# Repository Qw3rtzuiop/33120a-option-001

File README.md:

# 33120a-option-001
External reference frequency option for the HP/Agilent/Keysight 33120a arbitrary function generator

<span style="color:red">The calibration can fail with "value range" error. I solved it by repeating the calibration 86 multiple times changing the readout frequency in small and bigger steps.</span>

The ocxo is a used Vectron C4550A1-0213 (10 MHz, 5V).

Kicad 3d render pic of the rev. 1 PCB.

The PCB is mounted on the side. You need to drill holes into the metal to mount the PCB. The pics show the rev. 0 with two bodge wires. 

Suitable isolated BNC jacks are Amphenol 112252.

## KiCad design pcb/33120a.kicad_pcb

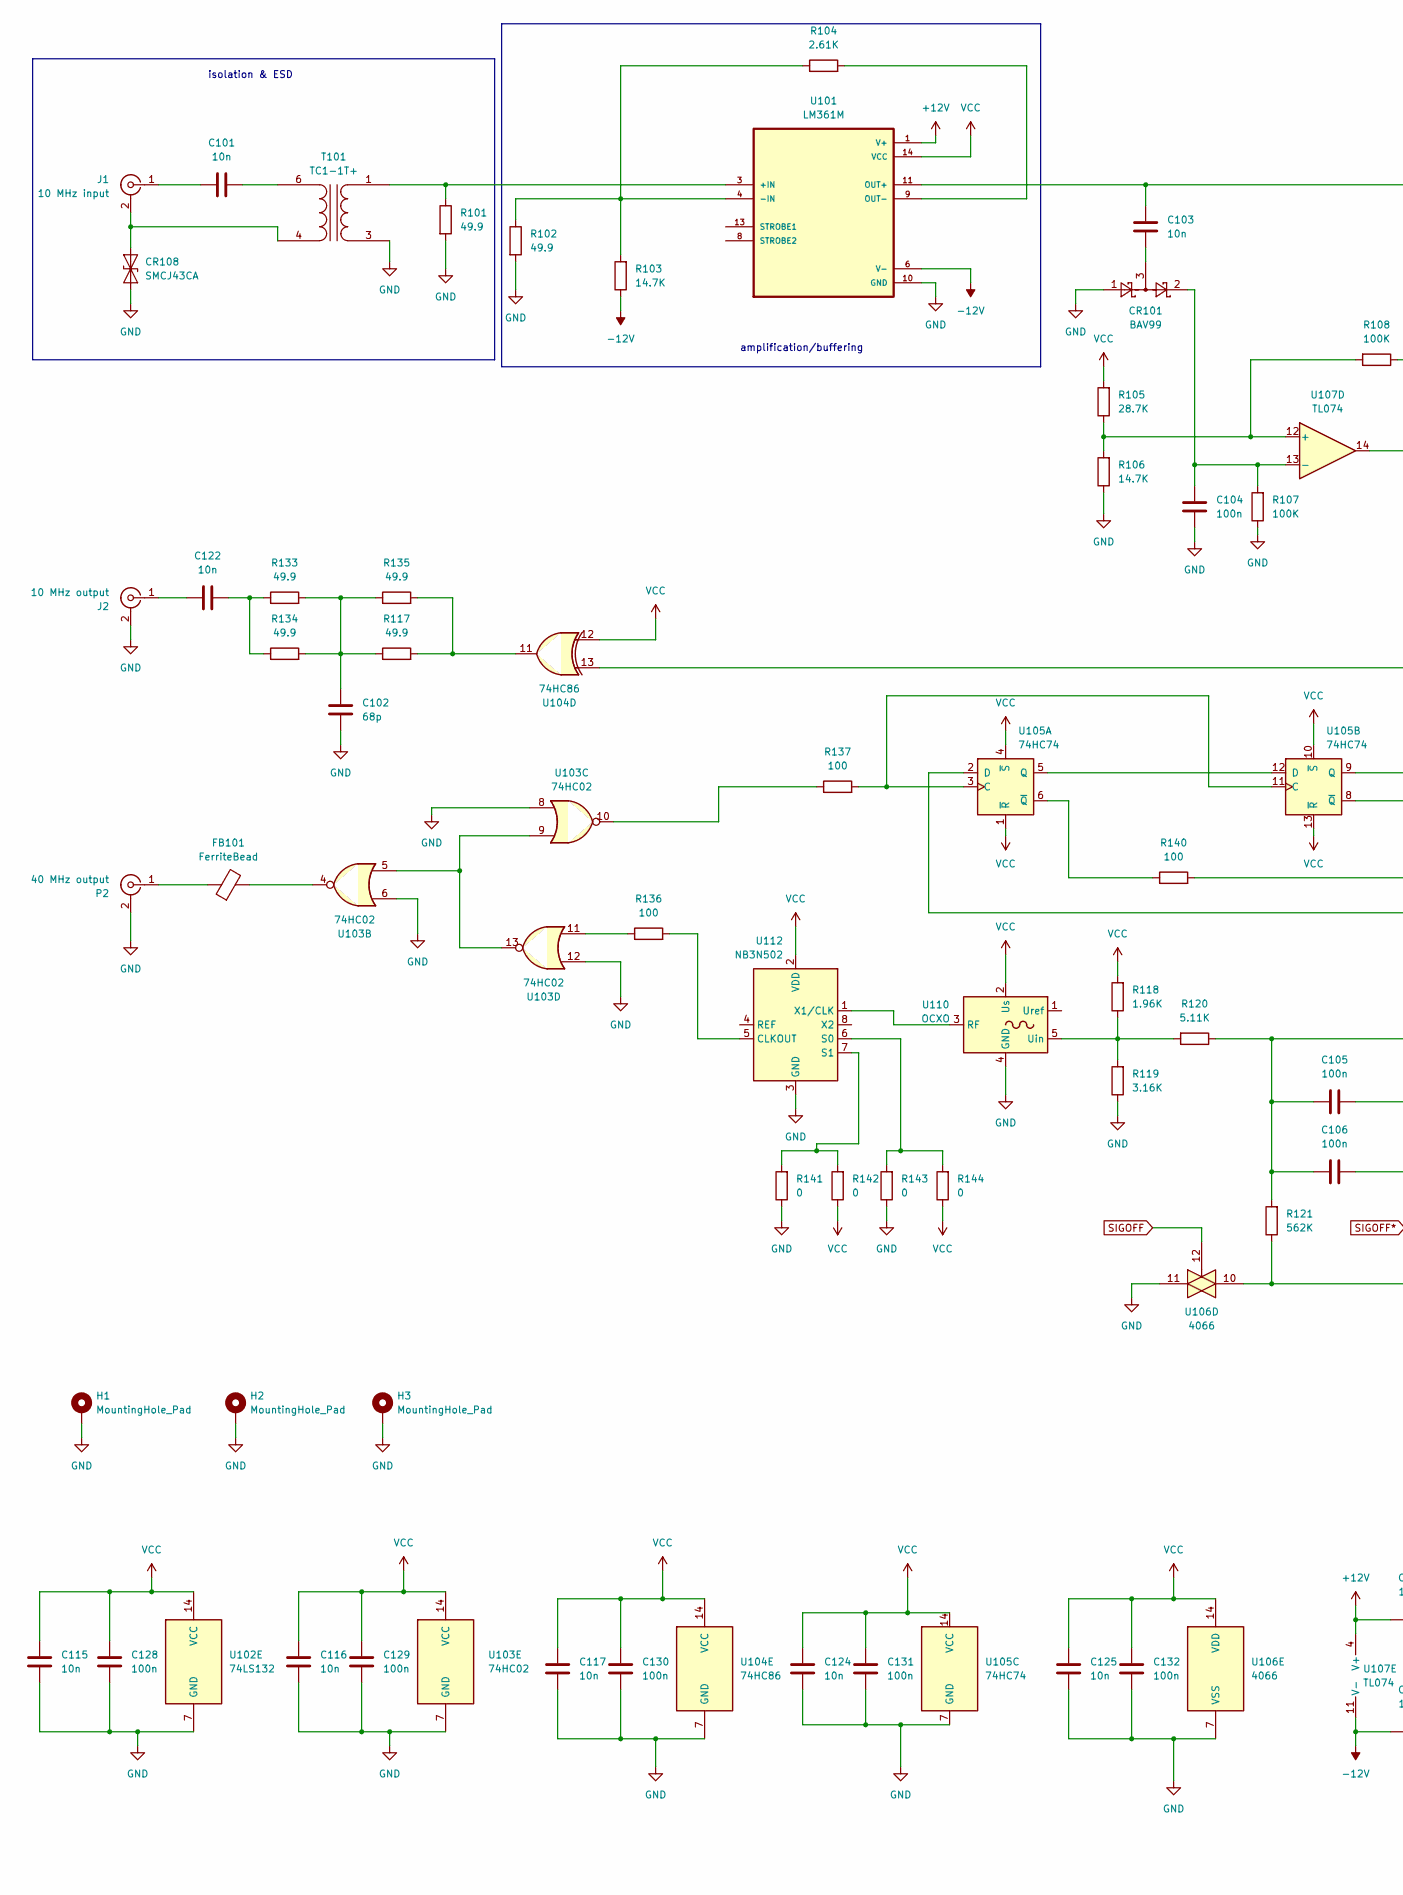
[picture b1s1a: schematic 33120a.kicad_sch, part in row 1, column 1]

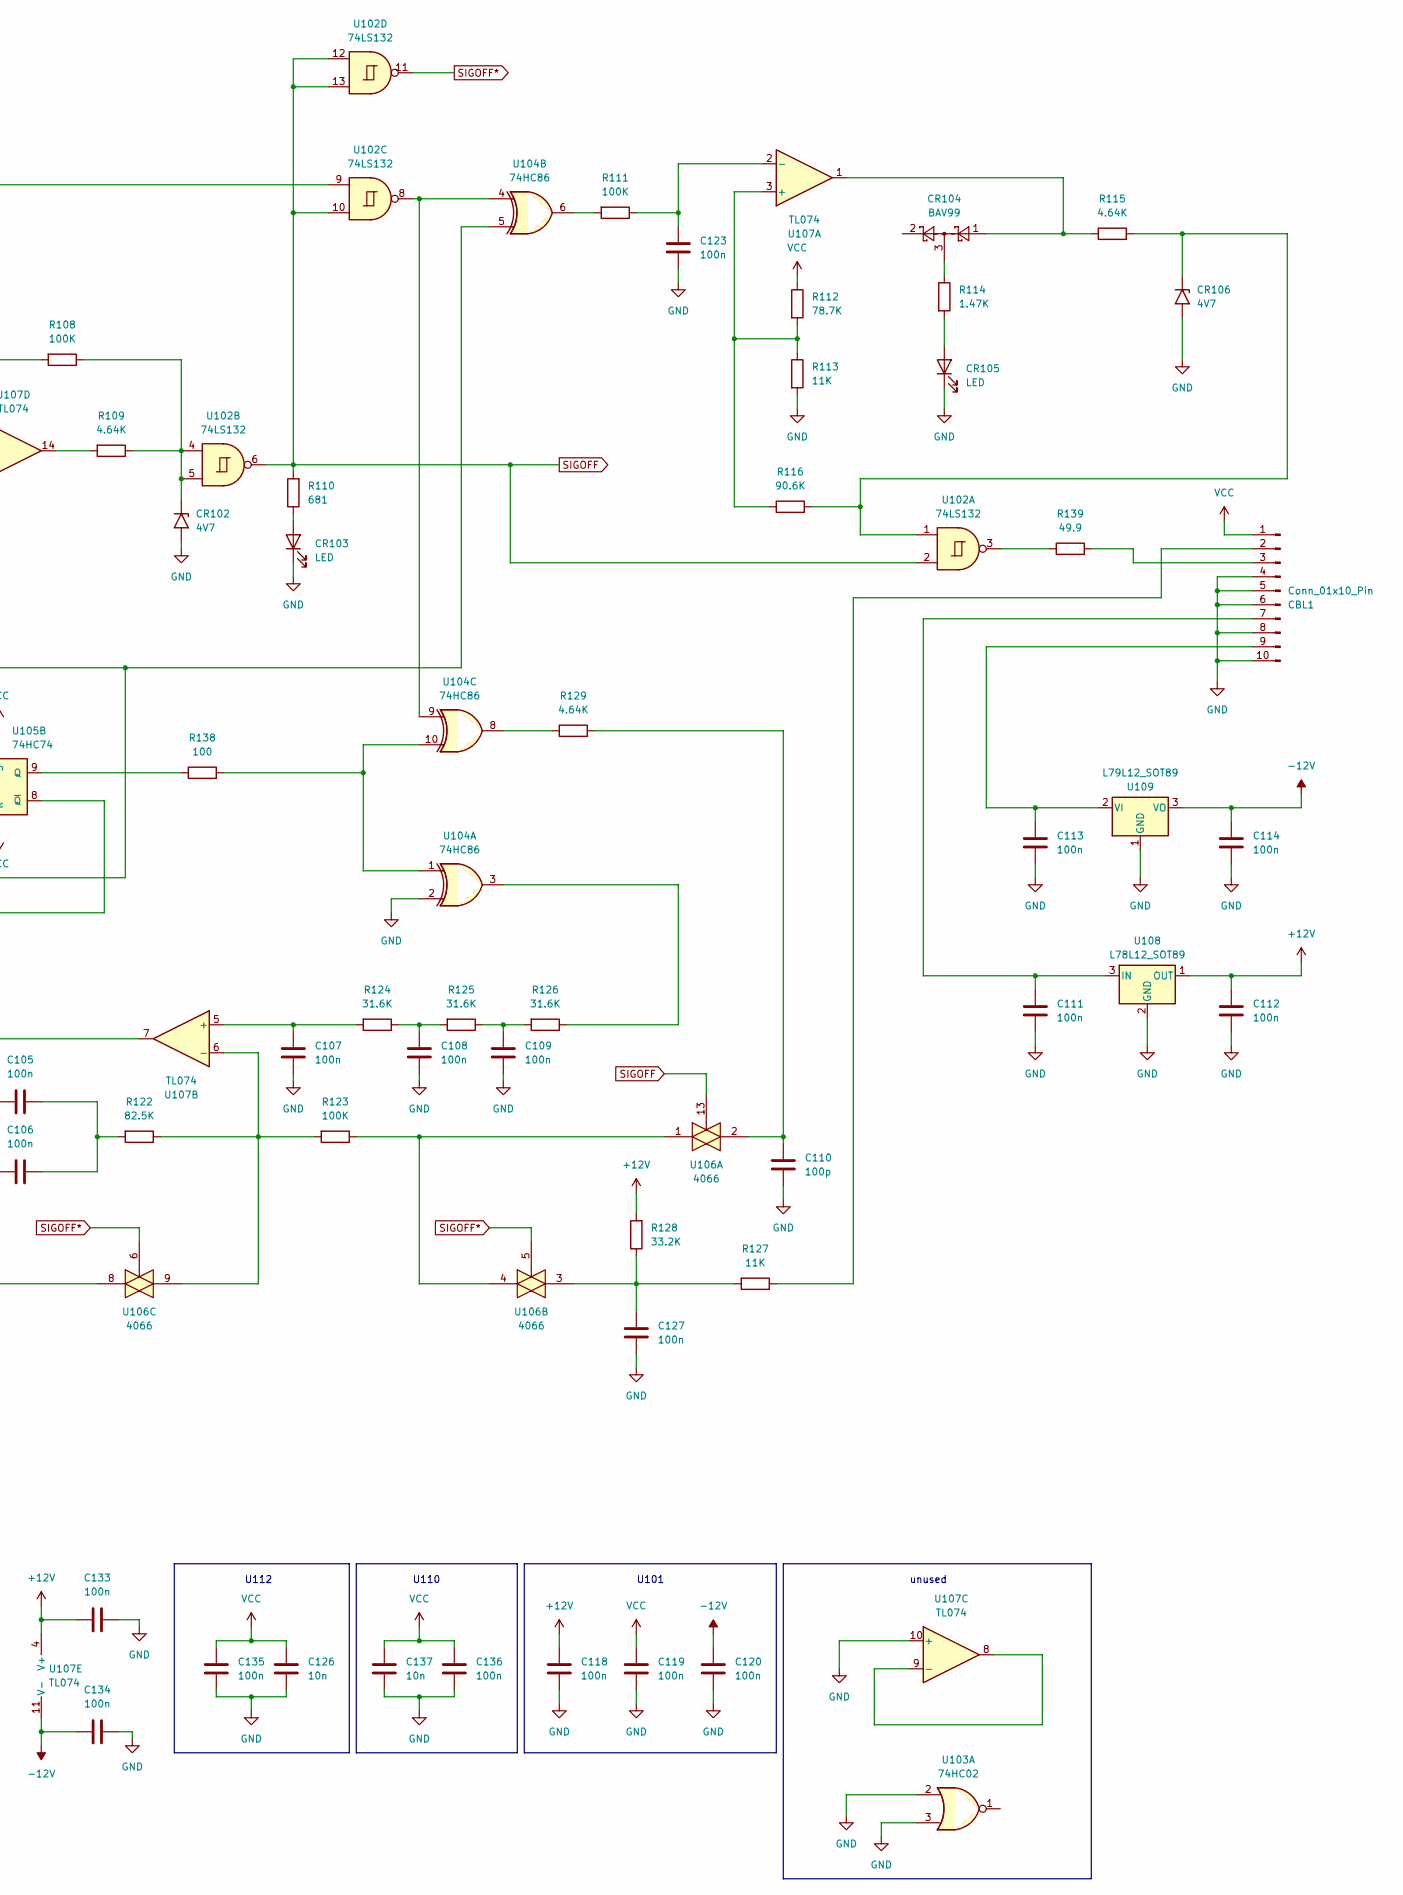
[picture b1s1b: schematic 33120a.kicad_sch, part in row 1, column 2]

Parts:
C101, C103, C115, C116, C117, C122, C124, C125, C126, C137: 10n; C_0805_2012Metric
C102: 68p; C_0805_2012Metric
C104, C105, C106, C107, C108, C109, C111, C112, C113, C114, C118, C119, C120, C123, C127, C128, C129, C130, C131, C132, C133, C134, C135, C136: 100n; C_0805_2012Metric
C110: 100p; C_0805_2012Metric
CBL1: Conn_01x10_Pin; IDC-Header_2x05_P2.54mm_Vertical
CR101, CR104: BAV99; SOT-23
CR102, CR106: 4V7; D_MiniMELF
CR103, CR105: LED; LED_0805_2012Metric
CR108: SMCJ43CA; D_SOD-128
FB101: FerriteBead; L_0805_2012Metric
H1, H2, H3: MountingHole_Pad; MountingHole_3.2mm_M3_DIN965_Pad_TopBottom
J1: 10 MHz input; SMA_Amphenol_901-144_Vertical
J2: 10 MHz output; SMA_Amphenol_901-144_Vertical
P2: 40 MHz output; SMA_Amphenol_901-144_Vertical
R101, R102, R117, R133, R134, R135, R139: 49.9; R_0805_2012Metric
R103, R106: 14.7K; R_0805_2012Metric
R104: 2.61K; R_0805_2012Metric
R105: 28.7K; R_0805_2012Metric
R107, R108, R111, R123: 100K; R_0805_2012Metric
R109, R115, R129: 4.64K; R_0805_2012Metric
R110: 681; R_0805_2012Metric
R112: 78.7K; R_0805_2012Metric
R113, R127: 11K; R_0805_2012Metric
R114: 1.47K; R_0805_2012Metric
R116: 90.6K; R_0805_2012Metric
R118: 1.96K; R_0805_2012Metric
R119: 3.16K; R_0805_2012Metric
R120: 5.11K; R_0805_2012Metric
R121: 562K; R_0805_2012Metric
R122: 82.5K; R_0805_2012Metric
R124, R125, R126: 31.6K; R_0805_2012Metric
R128: 33.2K; R_0805_2012Metric
R136, R137, R138, R140: 100; R_0805_2012Metric
R141, R142, R143, R144: 0; R_0805_2012Metric
T101: TC1-1T+; Transformer_MiniCircuits_AT224-1A
U101: LM361M; SOIC-14_3.9x8.7mm_P1.27mm
U102: 74LS132; SOIC-14_3.9x8.7mm_P1.27mm
U103: 74HC02; SOIC-14_3.9x8.7mm_P1.27mm
U104: 74HC86; SOIC-14_3.9x8.7mm_P1.27mm
U105: 74HC74; SOIC-14_3.9x8.7mm_P1.27mm
U106: 4066; SOIC-14_3.9x8.7mm_P1.27mm
U107: TL074; SOIC-14_3.9x8.7mm_P1.27mm
U108: L78L12_SOT89; SOT-89-3
U109: L79L12_SOT89; SOT-89-3
U110: OCXO; Oscillator_OCXO_Morion_MV317
U112: NB3N502; SOIC-8_3.9x4.9mm_P1.27mm

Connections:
+12V: C112.1, C118.1, C133.1, R128.2, U101.1 (V+), U107.4 (V+), U108.1 (OUT)
-12V: C114.1, C120.1, C134.1, R103.1, U101.6 (V-), U107.11 (V-), U109.3 (VO)
GND: C102.1, C104.2, C107.1, C108.1, C109.1, C110.1, C111.2, C112.2, C113.2, C114.2, C115.2, C116.2, C117.2, C118.2, C119.2, C120.2, C123.2, C124.2, C125.2, C126.2, C127.1, C128.2, C129.2, C130.2, C131.2, C132.2, C133.2, C134.2, C135.2, C136.2, C137.2, CBL1.4, CBL1.5, CBL1.6, CBL1.8, CBL1.10, CR101.1, CR102.2 (A2), CR103.1 (K), CR105.1 (K), CR106.2 (A2), CR108.1 (A1), H1.1, H2.1, H3.1, J2.2 (Ext), P2.2 (Ext), R101.2, R102.2, R106.1, R107.1, R113.2, R119.1, R141.1, R143.1, T101.3 (SA), U101.10 (GND), U102.7 (GND), U103.2, U103.3, U103.6, U103.7 (GND), U103.8, U103.12, U104.2, U104.7 (GND), U105.7 (GND), U106.7 (VSS), U106.11, U107.10 (+), U108.2 (GND), U109.1 (GND), U110.4 (GND), U112.3 (GND)
unnamed: C102.2, R117.1, R133.2, R134.2, R135.1
unnamed: C103.2, CR101.3
unnamed: C105.1, C106.1, R120.1, R121.2, U107.7
unnamed: C105.2, C106.2, R122.2
unnamed: C108.2, R124.1, R125.2
unnamed: C109.2, R125.1, R126.2
unnamed: C110.2, R129.2, U106.2
unnamed: C122.2, R133.1, R134.1
unnamed: C127.2, R127.2, R128.1, U106.3
unnamed: CBL1.2, R127.1
unnamed: CBL1.3, R139.2
unnamed: C111.1, CBL1.7, U108.3 (IN)
unnamed: C113.1, CBL1.9, U109.2 (VI)
unnamed: CR102.1 (A1), R108.1, R109.1, U102.4, U102.5
unnamed: CR103.2 (A), R110.1
unnamed: CR104.1, R115.1, U107.1
unnamed: CR104.3, R114.1
unnamed: CR105.2 (A), R114.2
unnamed: CR106.1 (A1), R115.2, R116.2, U102.1
unnamed: CR108.2 (A2), J1.2 (Ext), T101.4 (AB)
unnamed: FB101.2, U103.4
unnamed: C101.1, J1.1 (In)
unnamed: C122.1, J2.1 (In)
unnamed: FB101.1, P2.1 (In)
unnamed: R109.2, U107.14
unnamed: R111.2, U104.6
unnamed: R117.2, R135.2, U104.11
unnamed: R121.1, U106.8, U106.10
unnamed: R123.1, U106.1, U106.4
unnamed: R126.1, U104.3
unnamed: R129.1, U104.8
unnamed: R136.1, U103.11
unnamed: R137.1, U103.10
unnamed: R138.2, U104.1, U104.10
unnamed: R139.1, U102.3
unnamed: R140.2, U104.5, U104.13
unnamed: C101.2, T101.6 (AA)
unnamed: R101.1, T101.1 (SB), U101.3 (+IN)
unnamed: R102.1, R103.2, R104.1, U101.4 (-IN)
unnamed: C103.1, U101.11 (OUT+), U102.9
unnamed: R104.2, U101.9 (OUT-)
unnamed: U102.8, U104.4, U104.9
unnamed: U103.5, U103.9, U103.13
unnamed: R137.2, U105.3 (C), U105.11 (C)
unnamed: U105.2 (D), U105.8 (~Q)
unnamed: U105.5 (Q), U105.12 (D)
unnamed: R140.1, U105.6 (~Q)
unnamed: R138.1, U105.9 (Q)
unnamed: R112.2, R113.1, R116.1, U107.3 (+)
unnamed: C123.1, R111.1, U107.2 (-)
unnamed: C107.2, R124.2, U107.5 (+)
unnamed: R122.1, R123.2, U106.9, U107.6 (-)
unnamed: U107.8, U107.9 (-)
unnamed: R105.1, R106.2, R108.2, U107.12 (+)
unnamed: C104.1, CR101.2, R107.2, U107.13 (-)
unnamed: U110.3 (RF), U112.1 (X1/CLK)
unnamed: R118.1, R119.2, R120.2, U110.5 (Uin)
unnamed: R136.2, U112.5 (CLKOUT)
unnamed: R143.2, R144.2, U112.6 (S0)
unnamed: R141.2, R142.2, U112.7 (S1)
SIGOFF: R110.2, U102.2, U102.6, U102.10, U102.12, U102.13, U106.12, U106.13
SIGOFF*: U102.11, U106.5, U106.6
VCC: C115.1, C116.1, C117.1, C119.1, C124.1, C125.1, C126.1, C128.1, C129.1, C130.1, C131.1, C132.1, C135.1, C136.1, C137.1, CBL1.1, R105.2, R112.1, R118.2, R142.1, R144.1, U101.14 (VCC), U102.14 (VCC), U103.14 (VCC), U104.12, U104.14 (VCC), U105.1 (~R), U105.4 (~S), U105.10 (~S), U105.13 (~R), U105.14 (VCC), U106.14 (VDD), U110.2 (Us), U112.2 (VDD)

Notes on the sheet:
U101
U112
isolation & ESD
amplification/buffering
unused
U110

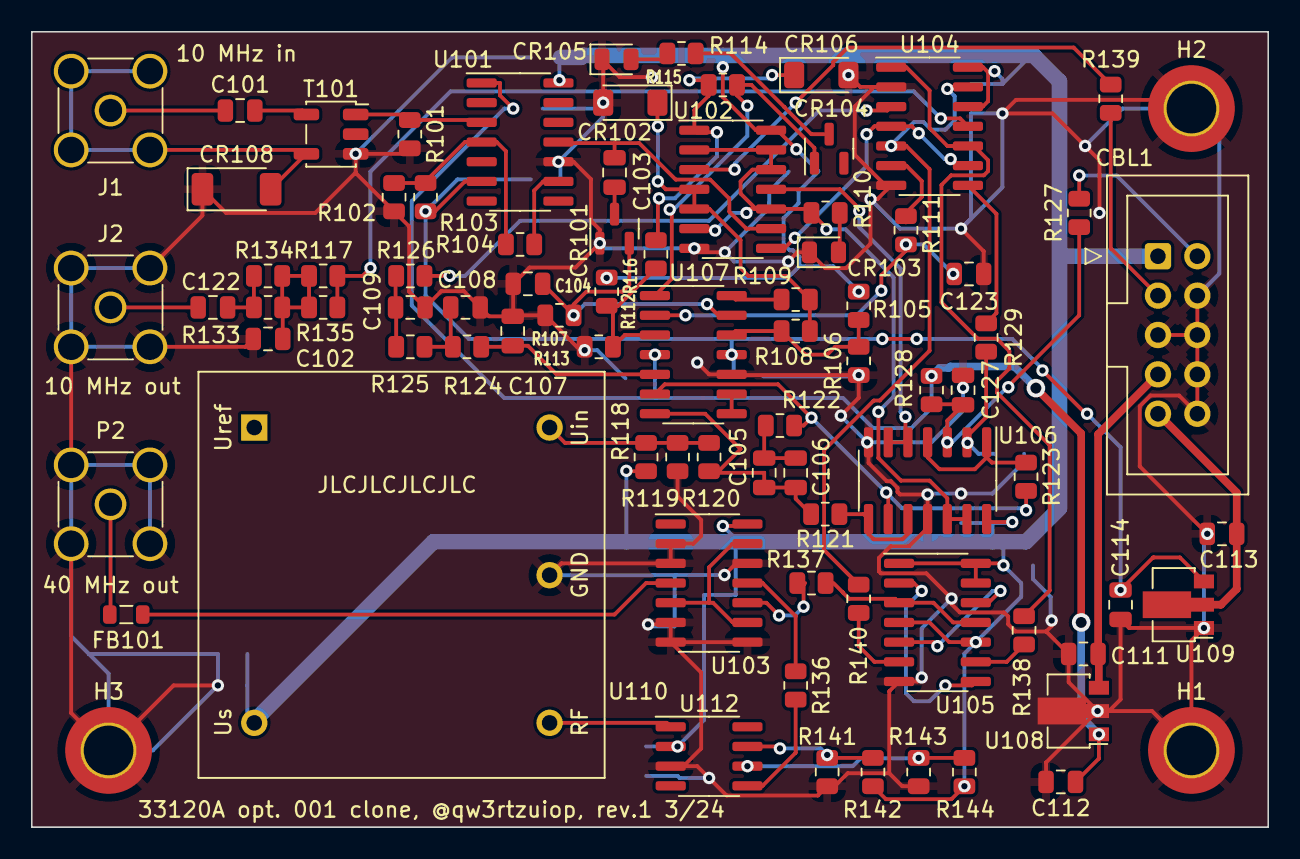
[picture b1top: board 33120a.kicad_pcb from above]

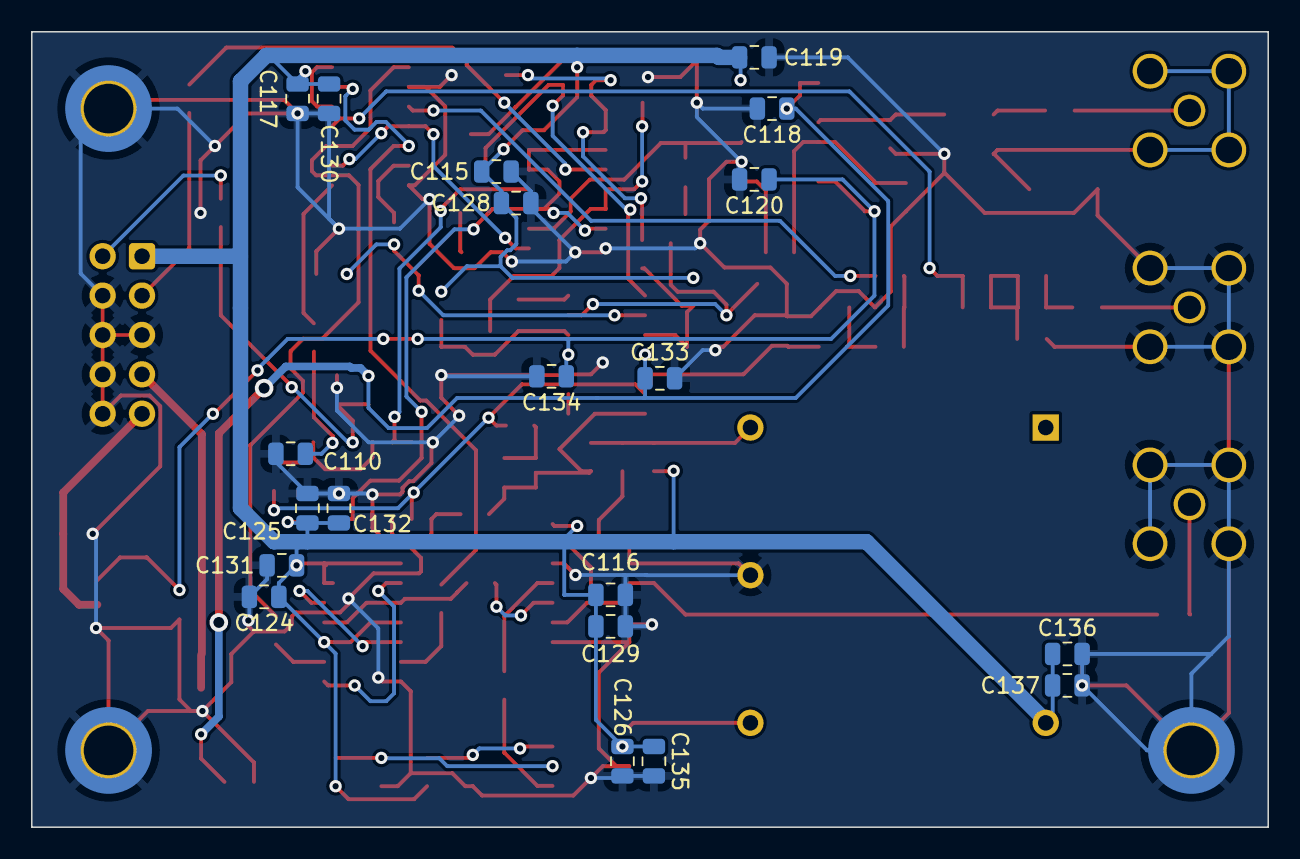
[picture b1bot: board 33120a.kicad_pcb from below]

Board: 2 copper layers, 79.8 x 51.3 mm, 104 parts (20 on the bottom side), 66 nets.

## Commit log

2024-03-08 rev. 1
2024-08-20 added info
2024-12-25 silkscreen update
2025-02-02 README.md aktualisiert
2025-03-12 edit readme
